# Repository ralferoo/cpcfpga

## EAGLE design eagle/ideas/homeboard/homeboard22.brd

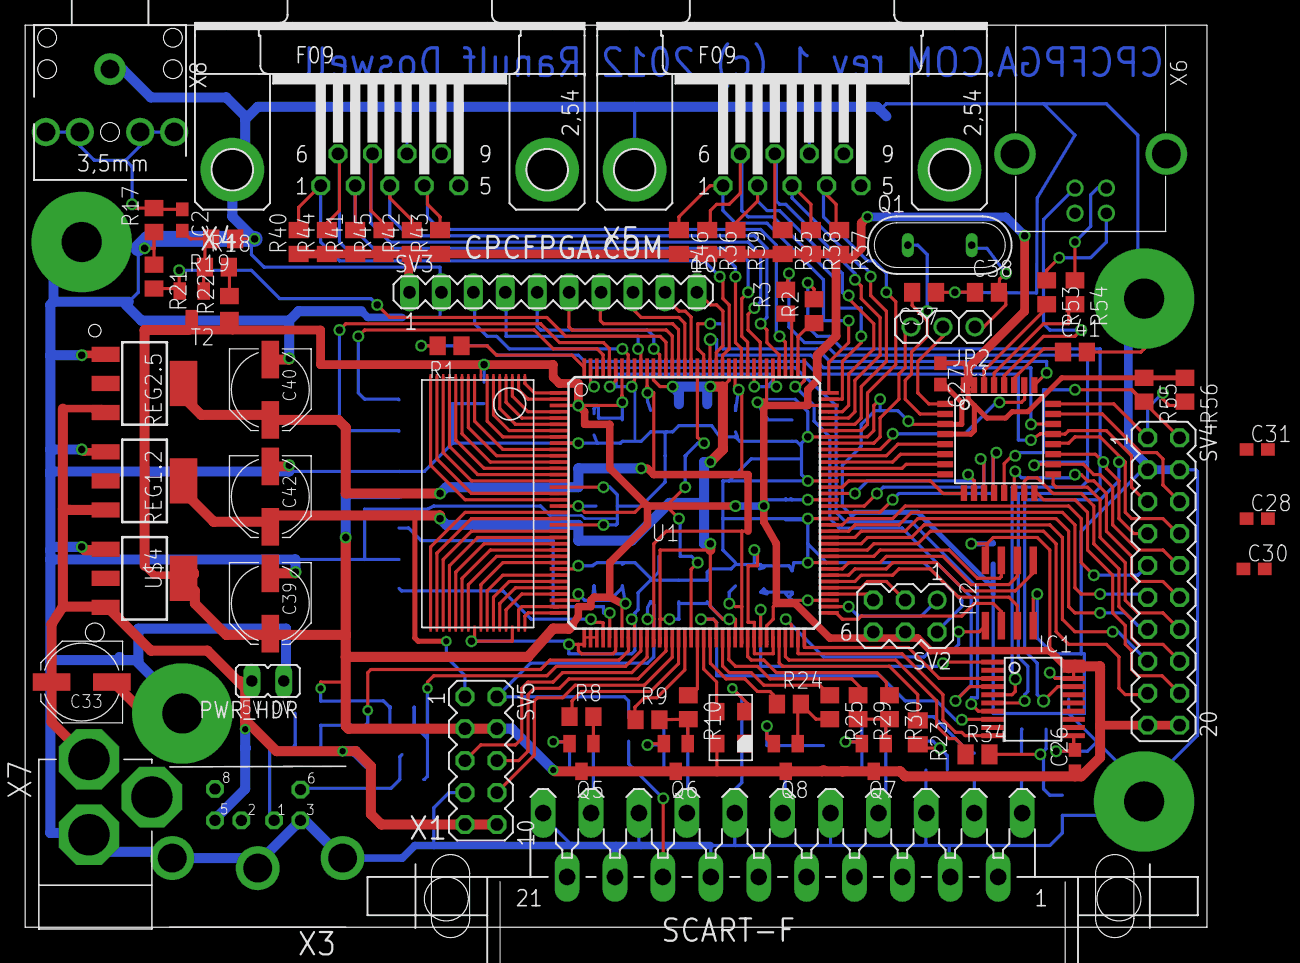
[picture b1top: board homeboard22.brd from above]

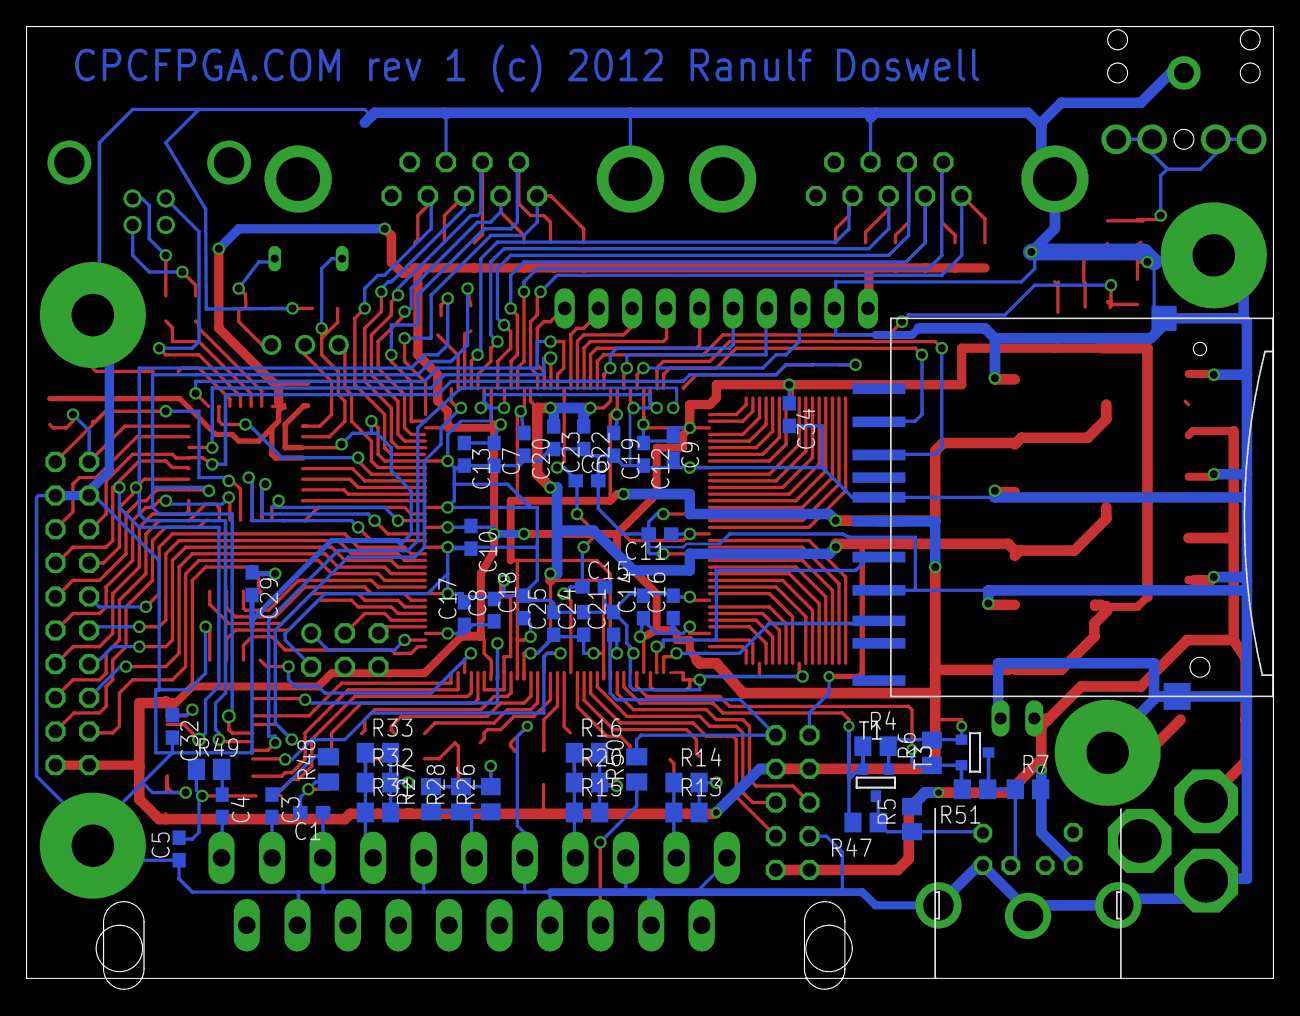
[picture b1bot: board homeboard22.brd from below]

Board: 2 copper layers, 94.0 x 72.6 mm, 128 parts (49 on the bottom side), 153 nets.

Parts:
C1, C3, C4, C5: C0603
C2, C6, C7, C8, C9, C10, C11, C12, C13, C14, C15, C16, C17, C18, C19, C20, C21, C22, C23, C24, C25, C26, C27, C28, C29, C30, C31, C32, C34: 100nF; C0603
C33, C39, C40, C42: 100u; PANASONIC_D
C37, C38: C0805
C41: 1uF; C0805
IC1: XCF02S; VO20
IC2: 25LC080SN; SO-08
IC3: ATMEGA32U2-TQFP; TQFP32-08
JP2: 1X03
PWR_HDR: JP1
Q1: QS
Q5, Q6, Q7, Q8: BC848SMD; SOT23
R1, R2, R3: 100; R0805
R4, R5, R6, R7, R10, R22, R25, R30: 1000; R0805
R8, R9, R14, R24, R29: 2200; R0805
R13, R16, R27, R32: 680; R0805
R15, R26, R31, R47, R51: 270; R0805
R17, R19: 10000; R0805
R18, R20, R28, R33, R55, R56: 4700; R0805
R21: 47000; R0805
R23, R34, R35, R36, R37, R38, R39, R40, R41, R42, R43, R44, R45, R46, R48, R49: M0805
R50: 2k2; M0805
R53, R54: 22; R0805
REG1.2: 1.2V; SOT223
REG2.5: 2.5V; SOT223
SV2: MA03-2
SV3: MA10-1
SV4: MA10-2
SV5: MA05-2
T1, T3: BSS138; SOT-23
T2: BC848; SOT23
U1: XC3S400TQ144; TQ144
U$1, U$7, U$8, U$9: GNDHOLE
U$2: TXO_7C; OSC_7C
U$3: SDMMCNOHOLE; SDCARD-NOHOLE
U$4: 3.3V; SOT223
U$6: AS6C4008; TSOP32
X1: SCART-CLIP
X3: M_DIN6
X4, X5: F09HP
X6: MINI-USB_4P-85-32004-10X; 85-32004-10X
X7: DC21MMX; DC-21MM
X8: STEREOJACK; 20-0137

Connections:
AT_CLKO: IC3.22, U1.P124
AT_RESET: IC3.24, R56.2, SV4.1
B0: R30.1, U1.P63
B1: R29.1, U1.P60
CASIN: R21.2, T2.2, U1.P131
CLK16: U1.P56, U$2.OUT
CLK_5V: R5.1, R47.1, T1.1, X3.6
CSYNC: R8.1, U1.P52
DATA_5V: R7.1, R51.1, T3.1, X3.1
EMER_BOOT: IC3.13, R55.2, SV4.2
EXP_A: SV5.5, U1.P47
EXP_B: SV5.6, U1.P50
EXP_C: SV5.8, U1.P51
EXTCLK: JP2.3, U1.P100
FL_DI: IC2.5, U1.P79
FL_DO: IC2.2, U1.P73
FL_HOLD: IC2.7, U1.P82
FL_SCLK: IC2.6, U1.P80
FL_SEL: IC2.1, U1.P70
FL_WP: IC2.3, U1.P78
FPGA_AUDIO_LEFT: R23.1, U1.P68
FPGA_AUDIO_RIGHT: R34.1, U1.P69
G0: R25.1, U1.P59
G1: R24.1, U1.P57
GND: C1.1, C5.1, C6.2, C7.2, C8.2, C9.2, C10.2, C11.2, C12.2, C13.2, C14.2, C15.2, C16.2, C17.2, C18.2, C19.2, C20.2, C21.2, C22.2, C23.2, C24.2, C25.2, C26.2, C27.2, C28.2, C29.2, C30.2, C31.2, C32.2, C33.-, C34.2, C37.1, C38.1, C39.-, C40.-, C41.2, C42.-, IC1.11, IC2.4, IC3.3, PWR_HDR.1, R17.1, R19.1, R21.1, REG1.2.1, REG2.5.1, SV2.2, SV3.2, SV4.3, SV4.4, SV5.7, U1.P9, U1.P16, U1.P22, U1.P29, U1.P37, U1.P38, U1.P39, U1.P42, U1.P45, U1.P64, U1.P67, U1.P81, U1.P88, U1.P94, U1.P101, U1.P114, U1.P117, U1.P136, U1.P139, U$1.GND, U$2.GND, U$3.3, U$3.6, U$3.MT1, U$3.MT3, U$4.1, U$6.P24, U$6.P30, U$7.GND, U$8.GND, U$9.GND, X1.4, X1.5, X1.9, X1.13, X1.14, X1.17, X1.18, X1.21, X3.3, X3.SH1, X3.SH2, X3.SH3, X4.8, X4.G1, X5.8, X5.G1, X7.3, X8.1
HDR_MISO: SV4.13, U1.P85
HDR_MOSI: SV4.17, U1.P83
HDR_SCLK: SV4.15, U1.P84
HDR_SEL: SV4.11, U1.P86
HDR_SPARE: SV4.9, U1.P87
JOY0_DOWN: R41.2, U1.P118, X4.2
JOY0_FIRE1: R45.2, U1.P116, X4.7
JOY0_FIRE2: R44.2, U1.P119, X4.6
JOY0_LEFT: R42.2, U1.P113, X4.3
JOY0_RIGHT: R43.2, U1.P112, X4.4
JOY0_UP: R40.2, U1.P122, X4.1
JOY1_DOWN: R39.1, U1.P105, X5.2
JOY1_FIRE1: R35.1, U1.P104, X5.7
JOY1_FIRE2: R36.1, U1.P107, X5.6
JOY1_LEFT: R38.1, U1.P103, X5.3
JOY1_RIGHT: R37.1, U1.P102, X5.4
JOY1_UP: R46.1, U1.P108, X5.1
unnamed: SV3.4, U1.P135
unnamed: SV3.5, U1.P132
unnamed: SV3.3, U1.P137
unnamed: SV3.6, U1.P130
unnamed: SV3.7, U1.P129
unnamed: SV3.8, U1.P128
unnamed: SV3.9, U1.P127
unnamed: IC3.1, JP2.2
unnamed: C41.1, IC3.27
unnamed: C37.2, IC3.2, Q1.1
unnamed: C38.2, JP2.1, Q1.2
unnamed: SV3.10, U1.P123
unnamed: IC1.3, U1.P72
unnamed: R53.1, X6.2
unnamed: IC1.10, U1.P71
unnamed: R2.1, U1.P110
unnamed: IC1.7, U1.P143
unnamed: R1.1, U1.P144
unnamed: R3.1, U1.P111
unnamed: IC3.29, R54.2
unnamed: C1.2, R23.2, R48.1
unnamed: C3.1, R48.2
unnamed: Q6.1, R9.2, R10.2
unnamed: Q6.2, R15.2, R16.2, R20.2
unnamed: Q8.1, R24.2, R25.2
unnamed: Q8.2, R26.2, R27.2, R28.2
unnamed: Q7.1, R29.2, R30.2
unnamed: Q7.2, R31.2, R32.2, R33.2
unnamed: Q5.2, R13.2, R14.2
unnamed: C2.2, R18.1, R19.2, T2.1
unnamed: C2.1, R17.2, X8.2, X8.3, X8.4, X8.5
unnamed: R18.2, R22.2
unnamed: Q5.1, R8.2
unnamed: C4.1, R49.2
unnamed: C5.2, R34.2, R49.1
unnamed: R54.1, X6.3
unnamed: U1.P1, U$6.P1
unnamed: IC3.30, R53.2
unnamed: IC3.28, X6.4
unnamed: U1.P2, U$6.P2
unnamed: U1.P4, U$6.P3
unnamed: U1.P5, U$6.P4
unnamed: U1.P6, U$6.P5
unnamed: U1.P7, U$6.P6
unnamed: U1.P8, U$6.P7
unnamed: U1.P10, U$6.P9
unnamed: U1.P11, U$6.P10
unnamed: U1.P12, U$6.P11
unnamed: U1.P13, U$6.P12
unnamed: U1.P14, U$6.P13
unnamed: U1.P15, U$6.P14
unnamed: U1.P17, U$6.P15
unnamed: U1.P18, U$6.P16
unnamed: U1.P20, U$6.P17
unnamed: U1.P21, U$6.P18
unnamed: U1.P23, U$6.P19
unnamed: U1.P24, U$6.P20
unnamed: U1.P25, U$6.P21
unnamed: U1.P26, U$6.P22
unnamed: U1.P27, U$6.P23
unnamed: U1.P28, U$6.P25
unnamed: U1.P30, U$6.P26
unnamed: U1.P31, U$6.P27
unnamed: U1.P32, U$6.P28
unnamed: U1.P33, U$6.P29
unnamed: U1.P35, U$6.P31
unnamed: U1.P36, U$6.P32
PC2: IC3.5, U1.P98
PC4: IC3.26, U1.P99
PC5: IC3.25, U1.P125
PD0: IC3.6, U1.P97
PD1: IC3.7, U1.P96
PD2: IC3.8, U1.P95
PD3: IC3.9, U1.P93
PD4: IC3.10, U1.P92
PD5: IC3.11, U1.P90
PD6: IC3.12, U1.P89
PROM_DO: IC1.1, U1.P65
PROM_INITB: IC1.8, U1.P58
PS2CLK: R4.1, R47.2, T1.2, U1.P46
PS2DAT: R6.1, R51.2, T3.2, U1.P44
R0: R10.1, U1.P55
R1: R9.1, U1.P53
SCART_BLANKING: R50.1, X1.16
SCART_BLUE: R31.1, R32.1, R33.1, X1.7
SCART_COMP: R13.1, R14.1, X1.19
SCART_GREEN: R26.1, R27.1, R28.1, X1.11
SCART_LEFT: C3.2, X1.3
SCART_RED: R15.1, R16.1, R20.1, X1.15
SCART_RIGHT: C4.2, X1.1
SD_CLK: U1.P41, U$3.5
SD_CS: U1.P141, U$3.1
SD_DI: U1.P140, U$3.2
SD_DO: U1.P40, U$3.7
SPI_MISO: IC3.17, SV4.14
SPI_MOSI: IC3.16, SV4.18
SPI_SCLK: IC3.15, SV4.16
SPI_SEL: IC3.14, SV4.12
TCK: IC1.6, IC3.19, R2.2, SV4.7
TDI_FPGA: IC3.21, R1.2, SV4.5
TDO_EXP: IC3.23, SV4.6
TDO_FPGA: IC1.4, U1.P109
TDO_PROM: IC1.17, IC3.20, SV4.8
TMS: IC1.5, IC3.18, R3.2, SV4.10
VCC: C6.1, C7.1, C8.1, C9.1, C10.1, C11.1, C12.1, C13.1, C14.1, C15.1, C16.1, C17.1, C26.1, C27.1, C28.1, C29.1, C30.1, C31.1, C32.1, C34.1, C39.+, IC1.18, IC1.19, IC1.20, IC2.8, IC3.4, IC3.31, IC3.32, Q5.3, Q6.3, Q7.3, Q8.3, R4.2, R6.2, R22.1, R35.2, R36.2, R37.2, R38.2, R39.2, R40.1, R41.1, R42.1, R43.1, R44.1, R45.1, R46.2, R55.1, R56.1, SV2.4, SV2.6, SV3.1, SV4.19, SV4.20, SV5.3, SV5.4, T1.3, T2.3, T3.3, U1.P3, U1.P19, U1.P34, U1.P43, U1.P54, U1.P66, U1.P75, U1.P91, U1.P106, U1.P115, U1.P126, U1.P138, U$2.VDD, U$3.4, U$4.4, U$6.P8
VCC5: C33.+, PWR_HDR.2, R5.2, R7.2, REG1.2.3, REG2.5.3, SV5.9, SV5.10, U$4.3, X3.5, X7.2
VCCAUX: C18.1, C19.1, C20.1, C21.1, C40.+, R50.2, REG2.5.4, SV5.2, U1.P48, U1.P62, U1.P120, U1.P134
VCCINT: C22.1, C23.1, C24.1, C25.1, C42.+, REG1.2.4, SV5.1, U1.P49, U1.P61, U1.P121, U1.P133
X3: SV2.5, U1.P76
X4: SV2.3, U1.P77
X8: SV2.1, U1.P74

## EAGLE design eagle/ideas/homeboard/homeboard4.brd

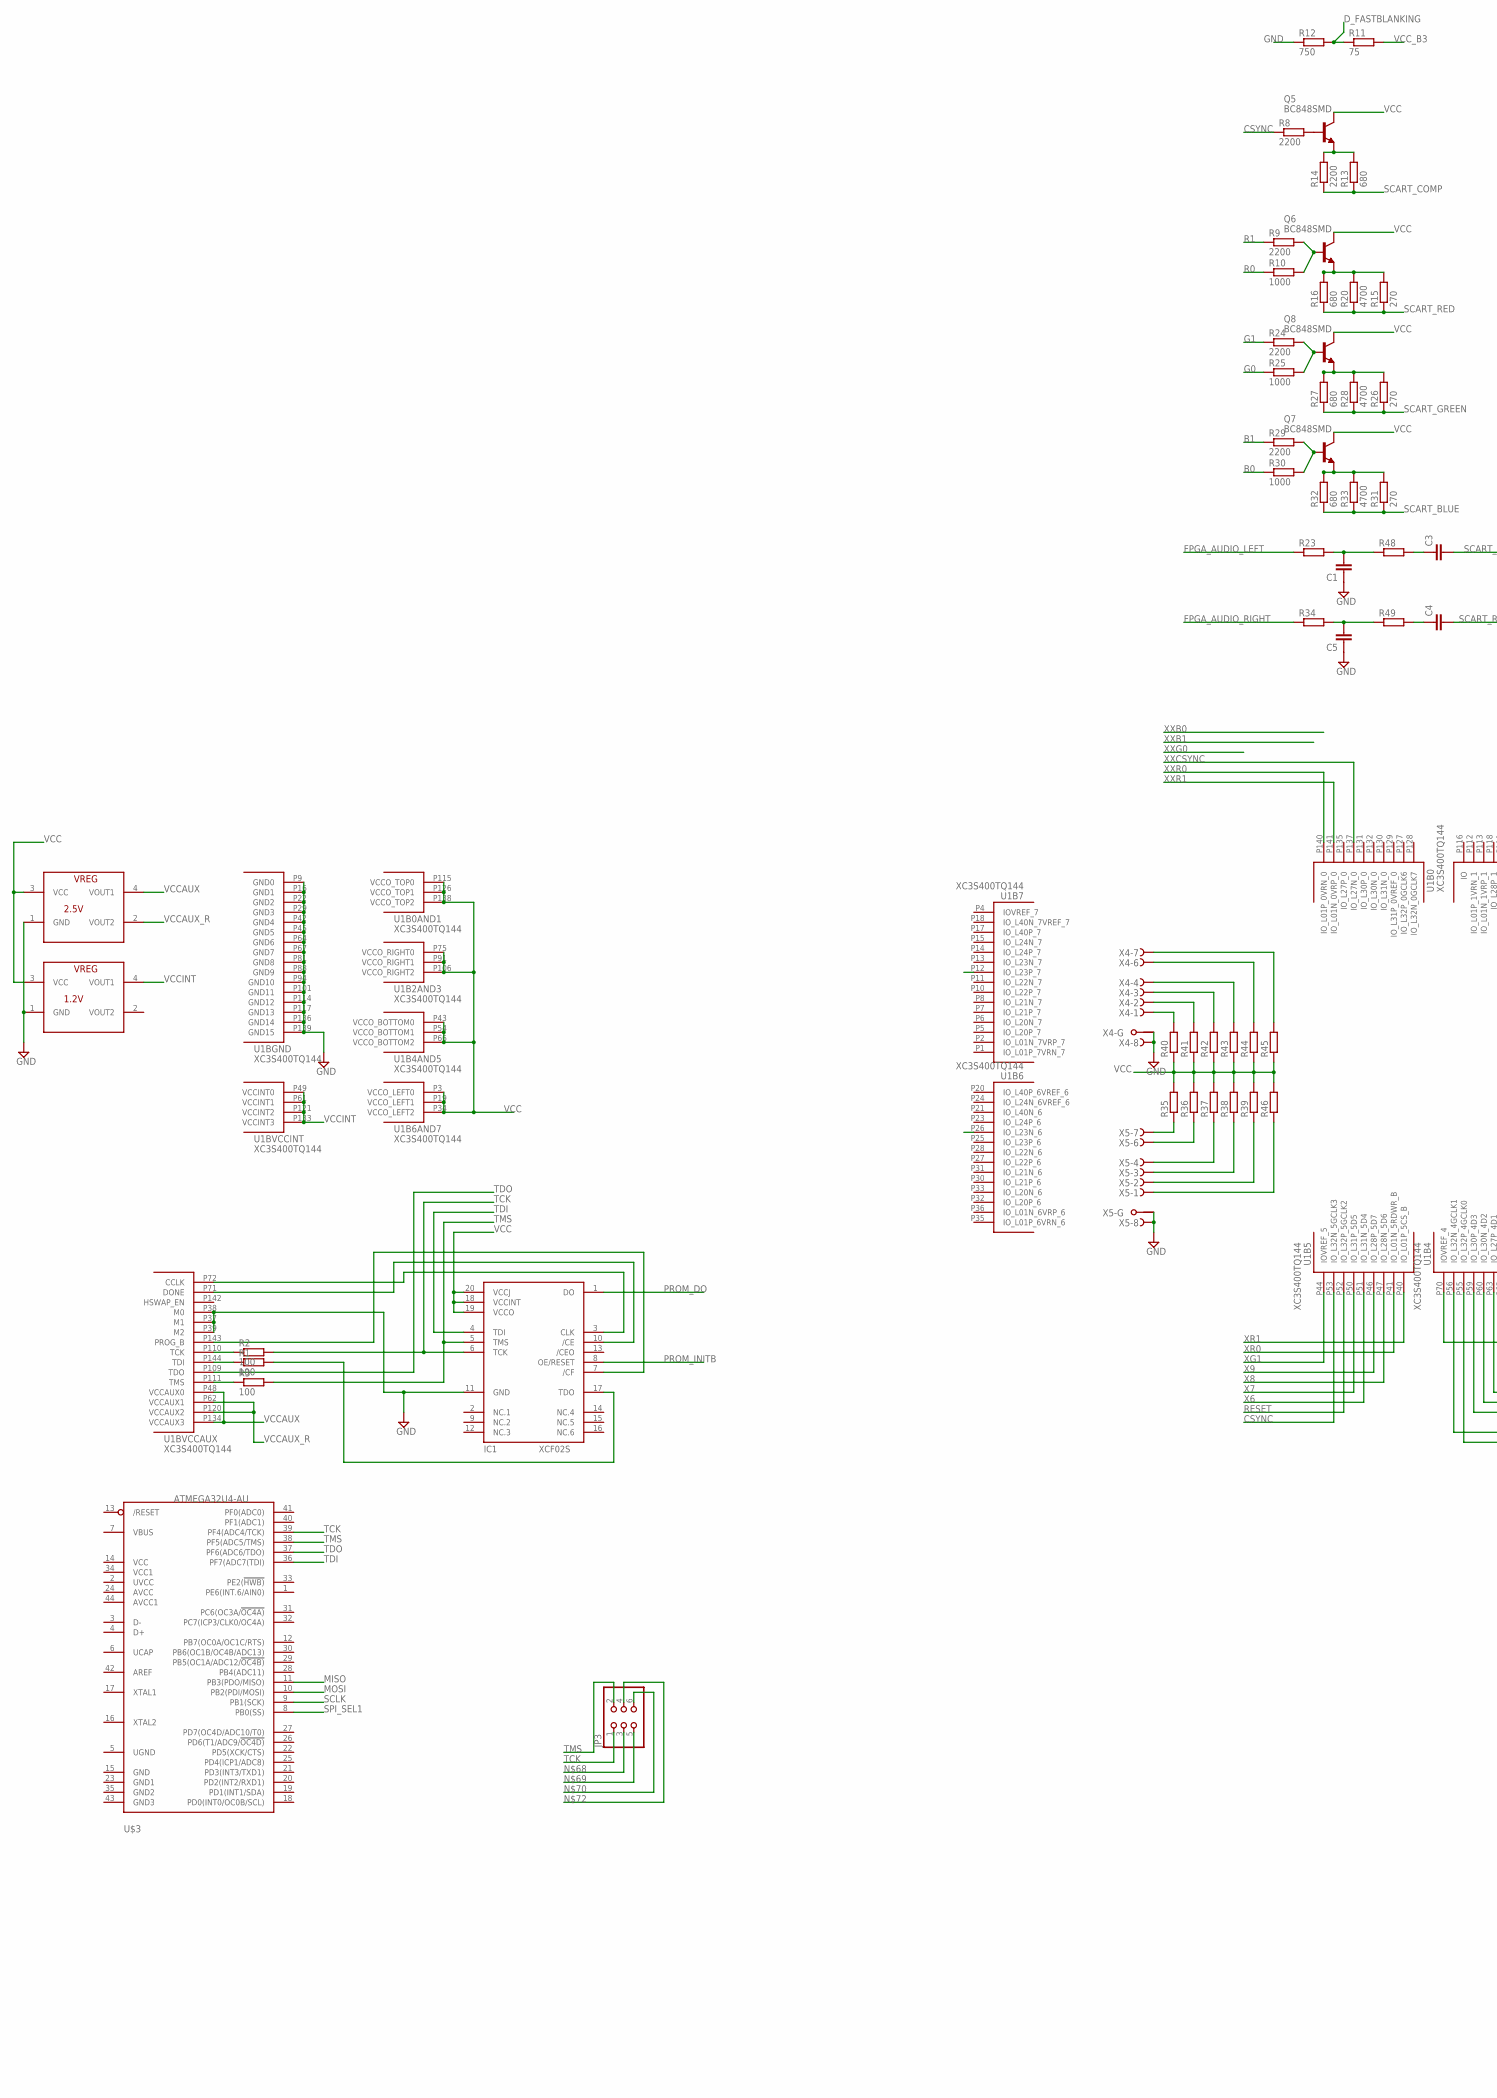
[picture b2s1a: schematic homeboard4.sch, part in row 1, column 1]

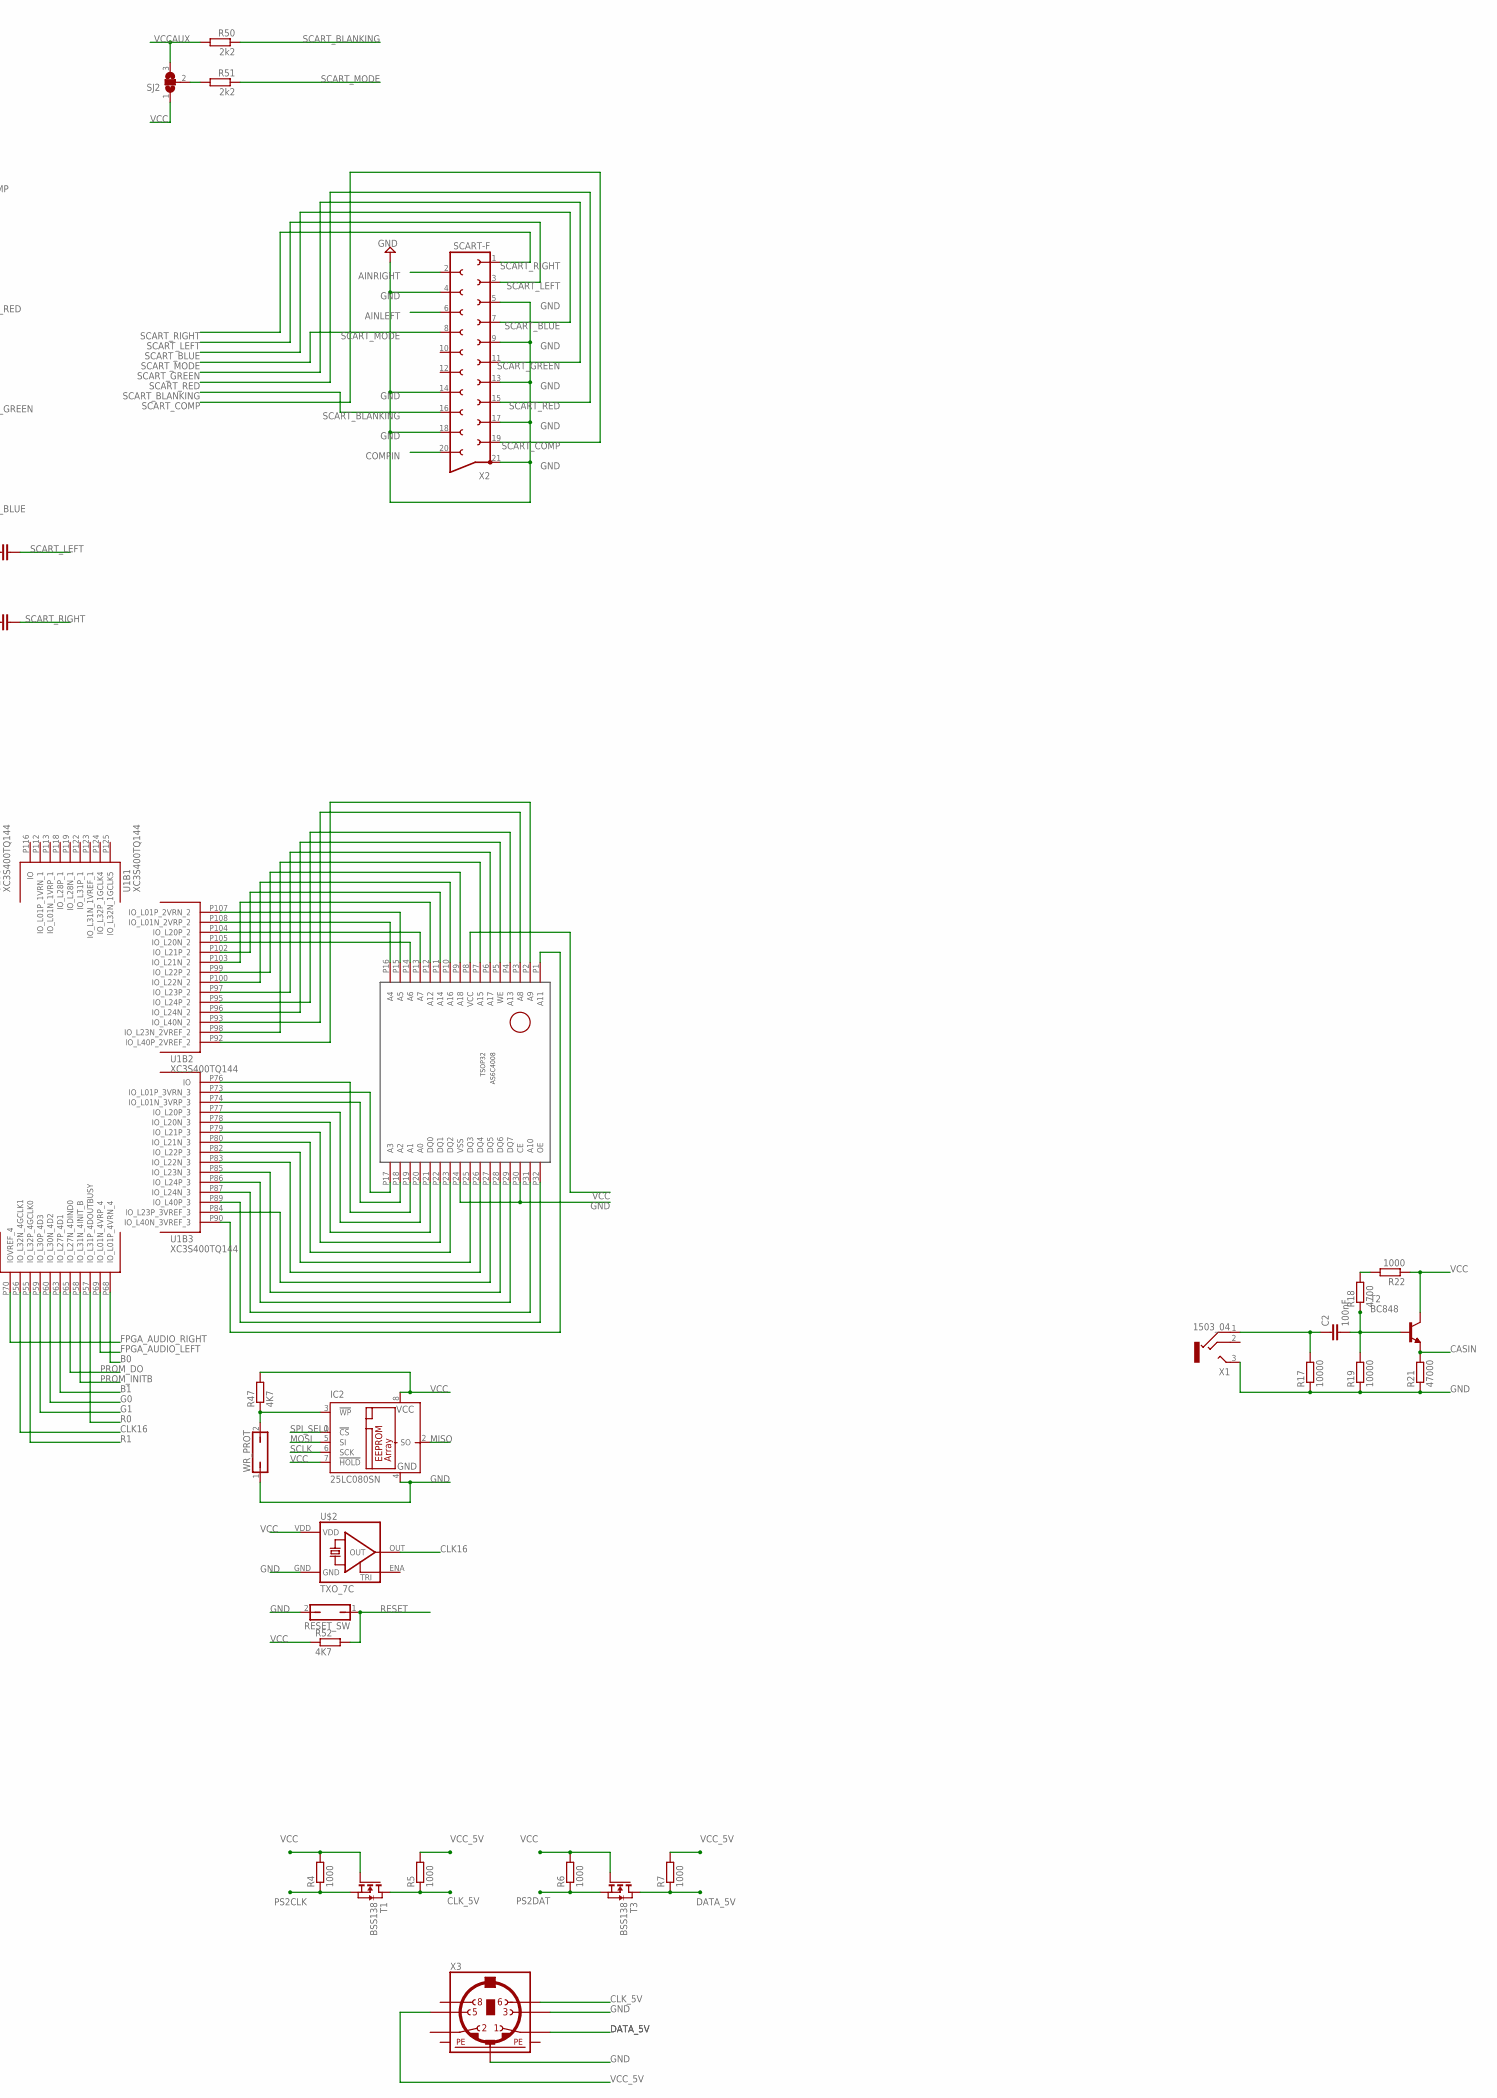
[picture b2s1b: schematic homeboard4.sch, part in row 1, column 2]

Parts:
C1, C3, C4, C5: C-EUC0603; C0603
C2: 100nF; C0603
IC1: XCF02S; VO20
IC2: 25LC080SN; SO-08
JP3: PINHD-2X3; 2X03
Q5, Q6, Q7, Q8: BC848SMD; SOT23
R1, R2, R3: 100; R0805
R4, R5, R6, R7, R10, R22, R25, R30: 1000; R0805
R8, R9, R14, R24, R29: 2200; R0805
R11: 75; R0805
R12: 750; R0805
R13, R16, R27, R32: 680; R0805
R15, R26, R31: 270; R0805
R17, R19: 10000; R0805
R18, R20, R28, R33: 4700; R0805
R21: 47000; R0805
R23, R34, R35, R36, R37, R38, R39, R40, R41, R42, R43, R44, R45, R46, R48, R49: R-EU_M0805; M0805
R47: 4K7; R0805
R50, R51: 2k2; M0805
R52: 4K7; M0805
REG1.2: 1.2V; SOT223
REG2.5: 2.5V; SOT223
RESET_SW: JP1Q; JP1
SJ2: SJ2W; SJ_2
T1, T3: BSS138; SOT-23
T2: BC848; SOT23
U1: XC3S400TQ144; TQ144
U$1: AS6C4008; TSOP32
U$2: TXO_7C; OSC_7C
U$3: ATMEGA32U4-AU; TQFP44
WR_PROT: JP1Q; JP1
X1: 1503_04
X2: SCART-F
X3: MINI_DIN_6; M_DIN6
X4, X5: F09HPS; F09HP

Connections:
AINLEFT: X2.6
AINRIGHT: X2.2
B0: R30.1, U1.P68 (IO_L01P_4VRN_4)
B1: R29.1, U1.P63 (IO_L27P_4D1)
CASIN: R21.2, T2.2 (E)
CLK16: U1.P56 (IO_L32N_4GCLK1), U$2.OUT
CLK_5V: R5.1, T1.1 (D), X3.6
COMPIN: X2.20
CSYNC: R8.1, U1.P53 (IO_L32N_5GCLK3)
DATA_5V: R7.1, T3.1 (D), X3.1
D_FASTBLANKING: R11.1, R12.2
FPGA_AUDIO_LEFT: R23.1, U1.P69 (IO_L01N_4VRP_4)
FPGA_AUDIO_RIGHT: R34.1, U1.P70 (IOVREF_4)
G0: R25.1, U1.P60 (IO_L30N_4D2)
G1: R24.1, U1.P59 (IO_L30P_4D3)
GND: C1.1, C5.1, IC1.11 (GND), IC2.4 (GND), R12.1, R17.1, R19.1, R21.1, REG1.2.1 (GND), REG2.5.1 (GND), RESET_SW.2, U1.P9 (GND0), U1.P16 (GND1), U1.P22 (GND2), U1.P29 (GND3), U1.P37 (M1), U1.P38 (M0), U1.P39 (M2), U1.P42 (GND4), U1.P45 (GND5), U1.P64 (GND6), U1.P67 (GND7), U1.P81 (GND8), U1.P88 (GND9), U1.P94 (GND10), U1.P101 (GND11), U1.P114 (GND12), U1.P117 (GND13), U1.P136 (GND14), U1.P139 (GND15), U$1.P24 (VSS), U$1.P30 (CE), U$2.GND, WR_PROT.1, X1.3 (2), X2.4, X2.5, X2.9, X2.13, X2.14, X2.17, X2.18, X2.21, X3.3, X3.SH2 (PE2), X4.8 (F), X4.G1, X5.8 (F), X5.G1
MISO: IC2.2 (SO), U$3.11 (PB3(PDO/MISO))
MOSI: IC2.5 (SI), U$3.10 (PB2(PDI/MOSI))
unnamed: U1.P108 (IO_L01N_2VRP_2), U$1.P16 (A4)
unnamed: U1.P107 (IO_L01P_2VRN_2), U$1.P15 (A5)
unnamed: U1.P105 (IO_L20N_2), U$1.P14 (A6)
unnamed: U1.P104 (IO_L20P_2), U$1.P13 (A7)
unnamed: U1.P103 (IO_L21N_2), U$1.P12 (A12)
unnamed: U1.P102 (IO_L21P_2), U$1.P11 (A14)
unnamed: U1.P100 (IO_L22N_2), U$1.P10 (A16)
unnamed: U1.P99 (IO_L22P_2), U$1.P9 (A18)
unnamed: U1.P98 (IO_L23N_2VREF_2), U$1.P7 (A15)
unnamed: U1.P97 (IO_L23P_2), U$1.P6 (A17)
unnamed: U1.P96 (IO_L24N_2), U$1.P5 (WE)
unnamed: U1.P95 (IO_L24P_2), U$1.P4 (A13)
unnamed: U1.P93 (IO_L40N_2), U$1.P3 (A8)
unnamed: U1.P92 (IO_L40P_2VREF_2), U$1.P2 (A9)
unnamed: U1.P90 (IO_L40N_3VREF_3), U$1.P1 (A11)
unnamed: U1.P73 (IO_L01P_3VRN_3), U$1.P17 (A3)
unnamed: U1.P74 (IO_L01N_3VRP_3), U$1.P18 (A2)
unnamed: U1.P76 (IO), U$1.P19 (A1)
unnamed: U1.P77 (IO_L20P_3), U$1.P20 (A0)
unnamed: U1.P78 (IO_L20N_3), U$1.P21 (DQ0)
unnamed: U1.P79 (IO_L21P_3), U$1.P22 (DQ1)
unnamed: U1.P80 (IO_L21N_3), U$1.P23 (DQ2)
unnamed: U1.P82 (IO_L22P_3), U$1.P25 (DQ3)
unnamed: U1.P83 (IO_L22N_3), U$1.P26 (DQ4)
unnamed: U1.P84 (IO_L23P_3VREF_3), U$1.P27 (DQ5)
unnamed: U1.P85 (IO_L23N_3), U$1.P28 (DQ6)
unnamed: U1.P86 (IO_L24P_3), U$1.P29 (DQ7)
unnamed: U1.P87 (IO_L24N_3), U$1.P31 (A10)
unnamed: U1.P89 (IO_L40P_3), U$1.P32 (OE)
unnamed: R35.1, X5.7 (F)
unnamed: R36.1, X5.6 (F)
unnamed: R37.1, X5.4 (F)
unnamed: R38.1, X5.3 (F)
unnamed: R39.1, X5.2 (F)
unnamed: IC1.3 (CLK), U1.P72 (CCLK)
unnamed: IC1.17 (TDO), R1.2
unnamed: R46.1, X5.1 (F)
unnamed: IC1.10 (/CE), U1.P71 (DONE)
unnamed: R2.1, U1.P110 (TCK)
unnamed: IC1.7 (/CF), U1.P143 (PROG_B)
unnamed: R40.2, X4.1 (F)
unnamed: R1.1, U1.P144 (TDI)
unnamed: R3.1, U1.P111 (TMS)
unnamed: R41.2, X4.2 (F)
unnamed: R42.2, X4.3 (F)
unnamed: R43.2, X4.4 (F)
unnamed: R44.2, X4.6 (F)
unnamed: R45.2, X4.7 (F)
unnamed: IC2.3 (!WP), R47.1, WR_PROT.2
unnamed: C1.2, R23.2, R48.1
unnamed: C3.1, R48.2
unnamed: Q6.1 (B), R9.2, R10.2
unnamed: Q6.2 (E), R15.2, R16.2, R20.2
unnamed: Q8.1 (B), R24.2, R25.2
unnamed: Q8.2 (E), R26.2, R27.2, R28.2
unnamed: Q7.1 (B), R29.2, R30.2
unnamed: Q7.2 (E), R31.2, R32.2, R33.2
unnamed: Q5.2 (E), R13.2, R14.2
unnamed: C2.2, R18.1, R19.2, T2.1 (B)
unnamed: C2.1, R17.2, X1.1
unnamed: R18.2, R22.2
unnamed: Q5.1 (B), R8.2
unnamed: C4.1, R49.2
unnamed: C5.2, R34.2, R49.1
unnamed: R51.2, SJ2.2
PE1: X3.SH1 (PE1)
PE3: X3.SH3 (PE3)
PROM_DO: IC1.1 (DO), U1.P65 (IO_L27N_4DIND0)
PROM_INITB: IC1.8 (OE/RESET), U1.P58 (IO_L31N_4INIT_B)
PS2CLK: R4.1, T1.2 (S)
PS2DAT: R6.1, T3.2 (S)
R0: R10.1, U1.P57 (IO_L31P_4DOUTBUSY)
R1: R9.1, U1.P55 (IO_L32P_4GCLK0)
RESET: R52.2, RESET_SW.1, U1.P52 (IO_L32P_5GCLK2)
SCART_BLANKING: R50.1, X2.16
SCART_BLUE: R31.1, R32.1, R33.1, X2.7
SCART_COMP: R13.1, R14.1, X2.19
SCART_GREEN: R26.1, R27.1, R28.1, X2.11
SCART_LEFT: C3.2, X2.3
SCART_MODE: R51.1, X2.8
SCART_RED: R15.1, R16.1, R20.1, X2.15
SCART_RIGHT: C4.2, X2.1
SCLK: IC2.6 (SCK), U$3.9 (PB1(SCK))
SPI_SEL0: IC2.1 (!CS)
SPI_SEL1: U$3.8 (PB0(SS))
TCK: IC1.6 (TCK), JP3.1, R2.2, U$3.39 (PF4(ADC4/TCK))
TDI: IC1.4 (TDI), U$3.36 (PF7(ADC7(TDI))
TDO: U1.P109 (TDO), U$3.37 (PF6(ADC6/TDO))
TMS: IC1.5 (TMS), JP3.2, R3.2, U$3.38 (PF5(ADC5/TMS))
VCC: IC1.18 (VCCINT), IC1.19 (VCCO), IC1.20 (VCCJ), IC2.7 (!HOLD), IC2.8 (VCC), Q5.3 (C), Q6.3 (C), Q7.3 (C), Q8.3 (C), R4.2, R6.2, R22.1, R35.2, R36.2, R37.2, R38.2, R39.2, R40.1, R41.1, R42.1, R43.1, R44.1, R45.1, R46.2, R47.2, R52.1, REG1.2.3 (VCC), REG2.5.3 (VCC), SJ2.1, T1.3 (G), T2.3 (C), T3.3 (G), U1.P3 (VCCO_LEFT0), U1.P19 (VCCO_LEFT1), U1.P34 (VCCO_LEFT2), U1.P43 (VCCO_BOTTOM0), U1.P54 (VCCO_BOTTOM1), U1.P66 (VCCO_BOTTOM2), U1.P75 (VCCO_RIGHT0), U1.P91 (VCCO_RIGHT1), U1.P106 (VCCO_RIGHT2), U1.P115 (VCCO_TOP0), U1.P126 (VCCO_TOP1), U1.P138 (VCCO_TOP2), U$1.P8 (VCC), U$2.VDD
VCCAUX: R50.2, REG2.5.4 (VOUT1), SJ2.3, U1.P48 (VCCAUX0), U1.P134 (VCCAUX3)
VCCAUX_R: REG2.5.2 (VOUT2), U1.P62 (VCCAUX1), U1.P120 (VCCAUX2)
VCCINT: REG1.2.4 (VOUT1), U1.P49 (VCCINT0), U1.P61 (VCCINT1), U1.P121 (VCCINT2), U1.P133 (VCCINT3)
VCC_5V: R5.2, R7.2, X3.5
VCC_B3: R11.2
X6: U1.P51 (IO_L31N_5D4)
X7: U1.P50 (IO_L31P_5D5)
X8: U1.P47 (IO_L28N_5D6)
X9: U1.P46 (IO_L28P_5D7)
XG1: U1.P44 (IOVREF_5)
XR0: U1.P41 (IO_L01N_5RDWR_B)
XR1: U1.P40 (IO_L01P_5CS_B)
XXCSYNC: U1.P137 (IO_L27N_0)
XXR0: U1.P140 (IO_L01P_0VRN_0)
XXR1: U1.P141 (IO_L01N_0VRP_0)

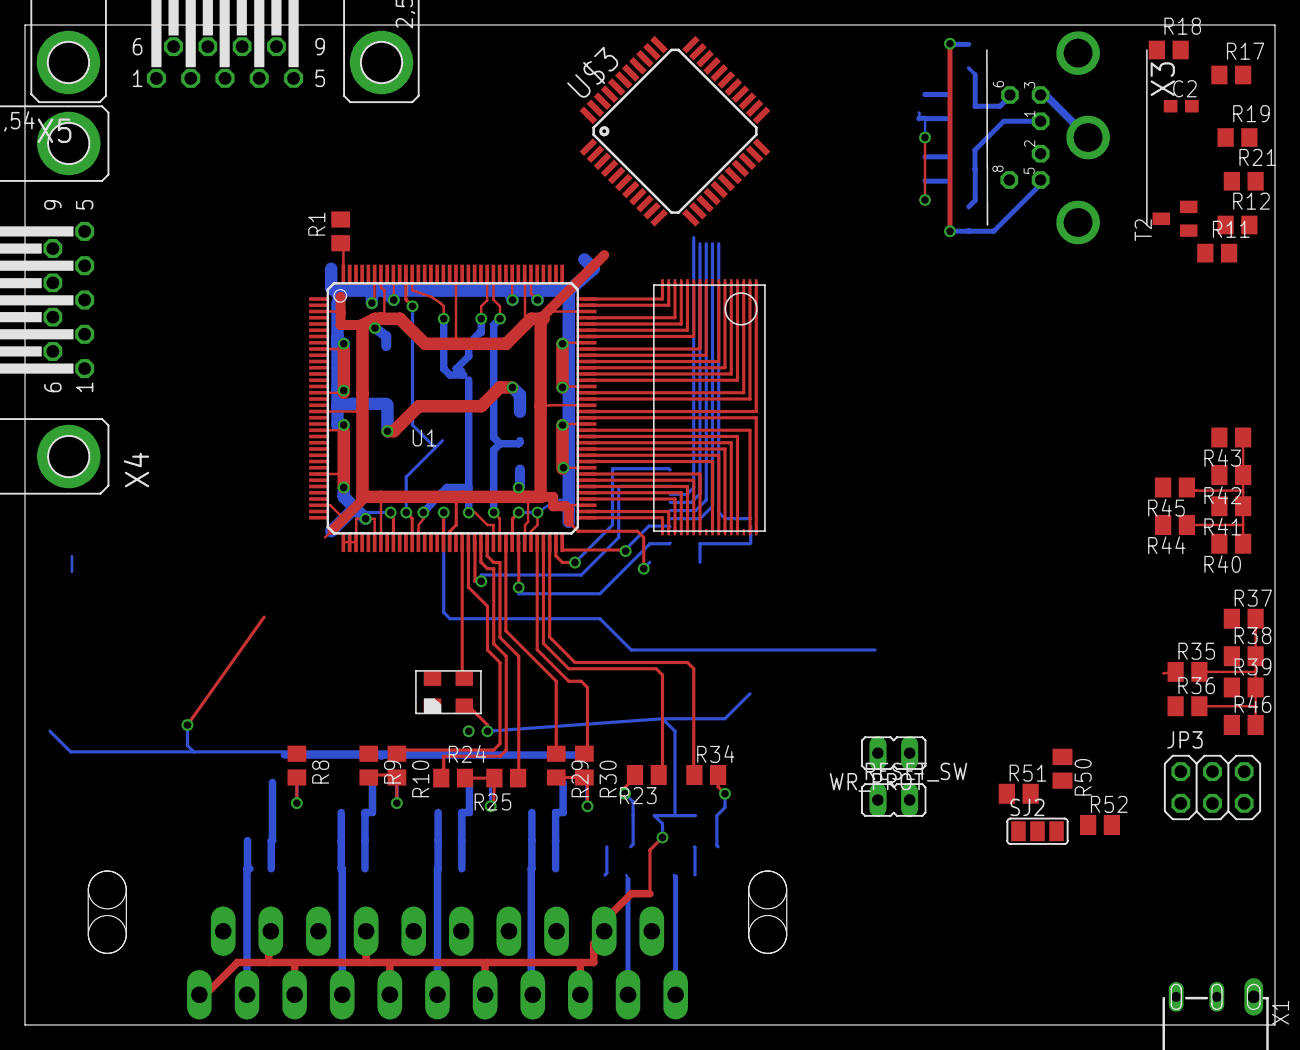
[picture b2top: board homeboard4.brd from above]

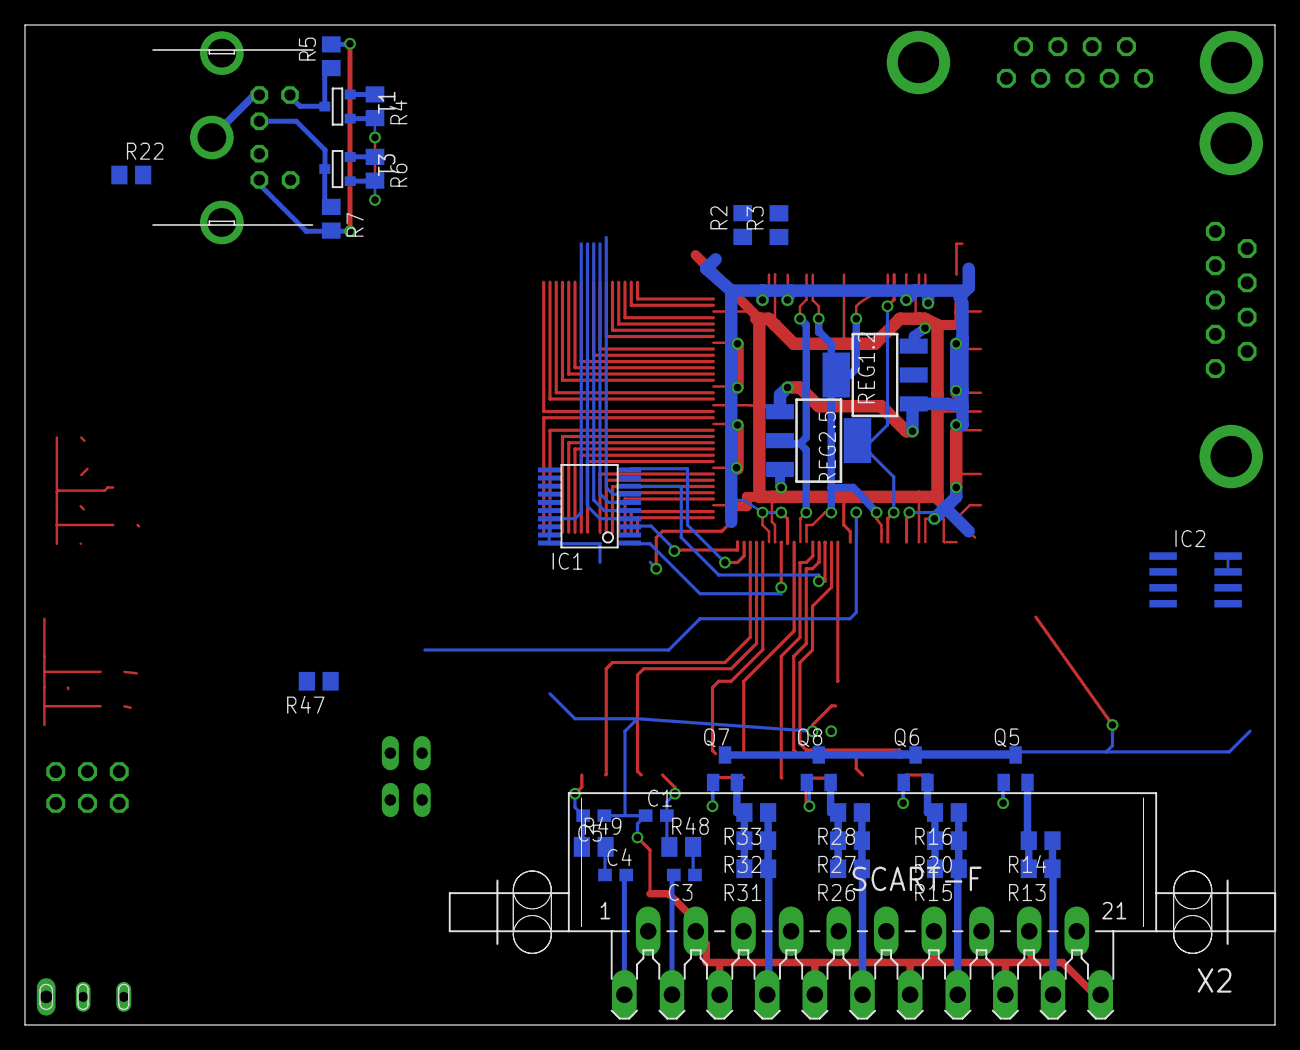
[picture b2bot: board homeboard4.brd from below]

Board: 2 copper layers, 100.0 x 80.0 mm, 81 parts (36 on the bottom side), 105 nets.

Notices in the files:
eagle/ideas/homeboard/homeboard22.brd:
CPCFPGA.COM rev 1 (c) 2012 Ranulf Doswell
